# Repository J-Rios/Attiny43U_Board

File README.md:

# Attiny43U_Board
An Attiny43U based AVR development board

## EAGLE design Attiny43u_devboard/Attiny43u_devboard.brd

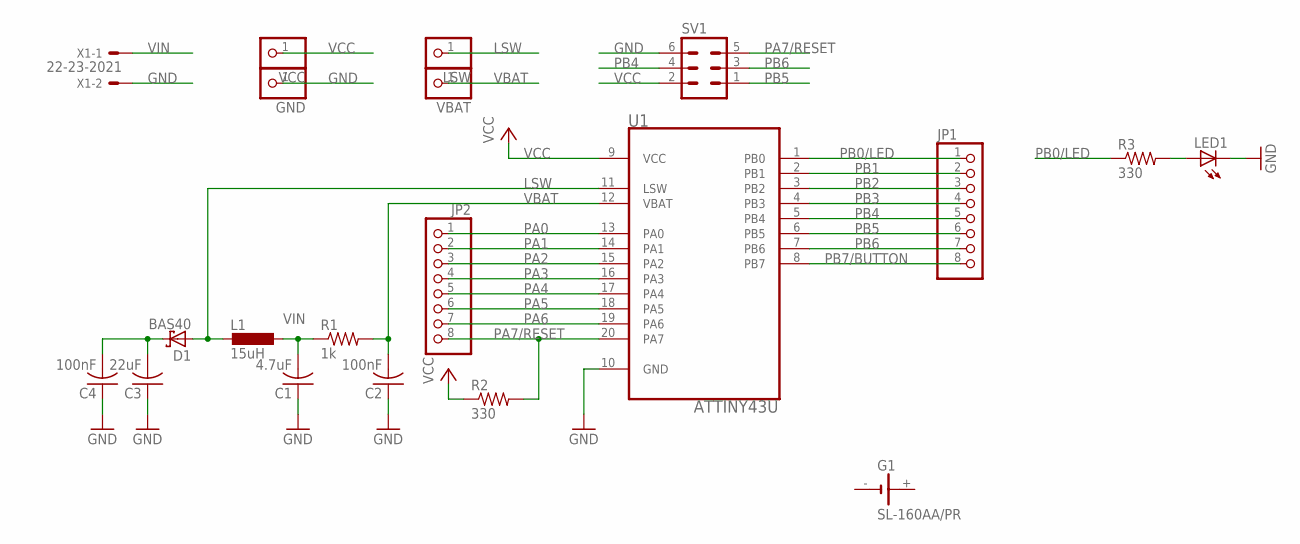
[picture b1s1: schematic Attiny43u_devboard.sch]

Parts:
C1: 4.7uF; C1206K
C2, C4: 100nF; C1206K
C3: 22uF; C1206K
D1: BAS40; SOT23
G1: SL-160AA/PR
GND: PINHD-1X1; 1X01
JP1, JP2: PINHD-1X8; 1X08
L1: 15uH; L3225M
LED1: LEDCHIPLED_1206; CHIPLED_1206
LSW: PINHD-1X1; 1X01
R1: 1k; M1206
R2, R3: 330; M1206
SV1: MA03-2
U1: ATTINY43U; SOIC127P1032X265-20N
VBAT: PINHD-1X1; 1X01
VCC: PINHD-1X1; 1X01
X1: 22-23-2021

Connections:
GND: C1.1, C2.1, C3.1, C4.1, GND.1, LED1.C, SV1.6, U1.10 (GND), X1.2
LSW: D1.1 (A), L1.2, LSW.1, U1.11 (LSW)
unnamed: LED1.A, R3.2
unnamed: C3.2, C4.2, D1.3 (C)
PA0: JP2.1, U1.13 (PA0)
PA1: JP2.2, U1.14 (PA1)
PA2: JP2.3, U1.15 (PA2)
PA3: JP2.4, U1.16 (PA3)
PA4: JP2.5, U1.17 (PA4)
PA5: JP2.6, U1.18 (PA5)
PA6: JP2.7, U1.19 (PA6)
PA7/RESET: JP2.8, R2.2, SV1.5, U1.20 (PA7)
PB0/LED: JP1.1, R3.1, U1.1 (PB0)
PB1: JP1.2, U1.2 (PB1)
PB2: JP1.3, U1.3 (PB2)
PB3: JP1.4, U1.4 (PB3)
PB4: JP1.5, SV1.4, U1.5 (PB4)
PB5: JP1.6, SV1.1, U1.6 (PB5)
PB6: JP1.7, SV1.3, U1.7 (PB6)
PB7/BUTTON: JP1.8, U1.8 (PB7)
VBAT: C2.2, R1.2, U1.12 (VBAT), VBAT.1
VCC: R2.1, SV1.2, U1.9 (VCC), VCC.1
VIN: C1.2, L1.1, R1.1, X1.1

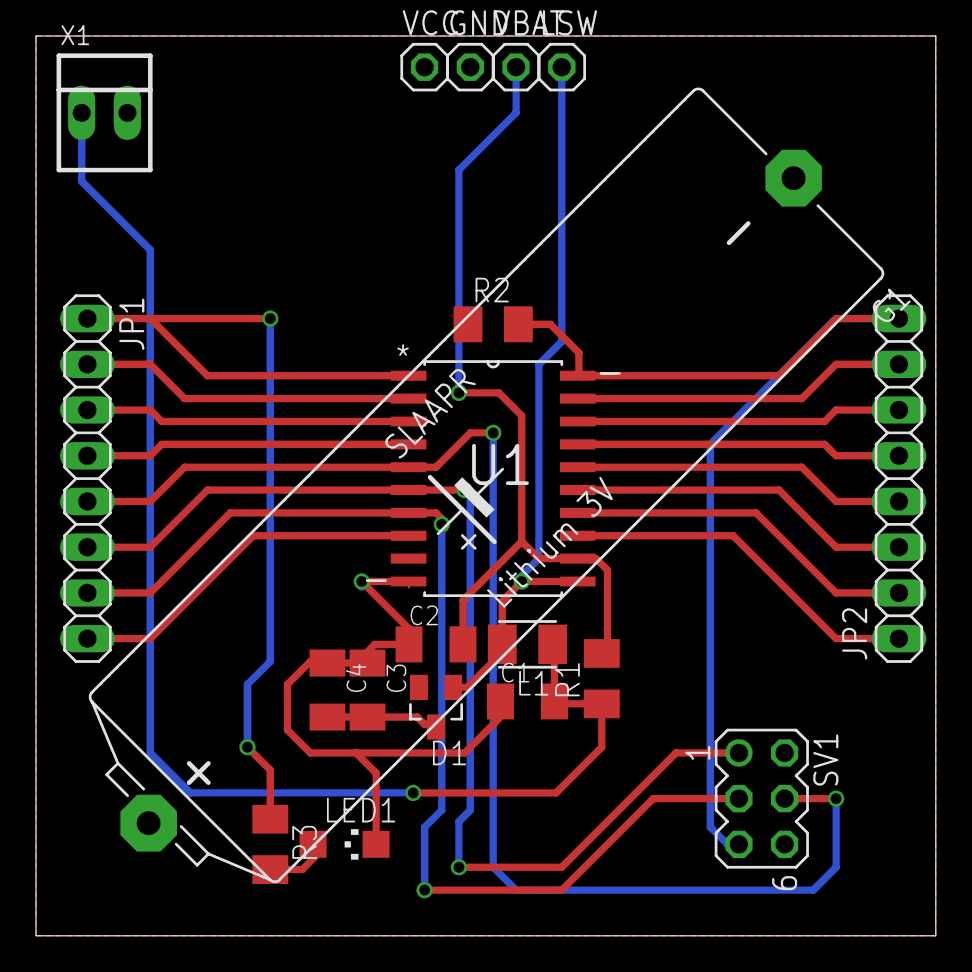
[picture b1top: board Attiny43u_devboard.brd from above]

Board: 2 copper layers, 50.0 x 50.0 mm, 20 parts (0 on the bottom side), 23 nets.

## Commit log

2015-05-14 Board added
    Eagle project added
